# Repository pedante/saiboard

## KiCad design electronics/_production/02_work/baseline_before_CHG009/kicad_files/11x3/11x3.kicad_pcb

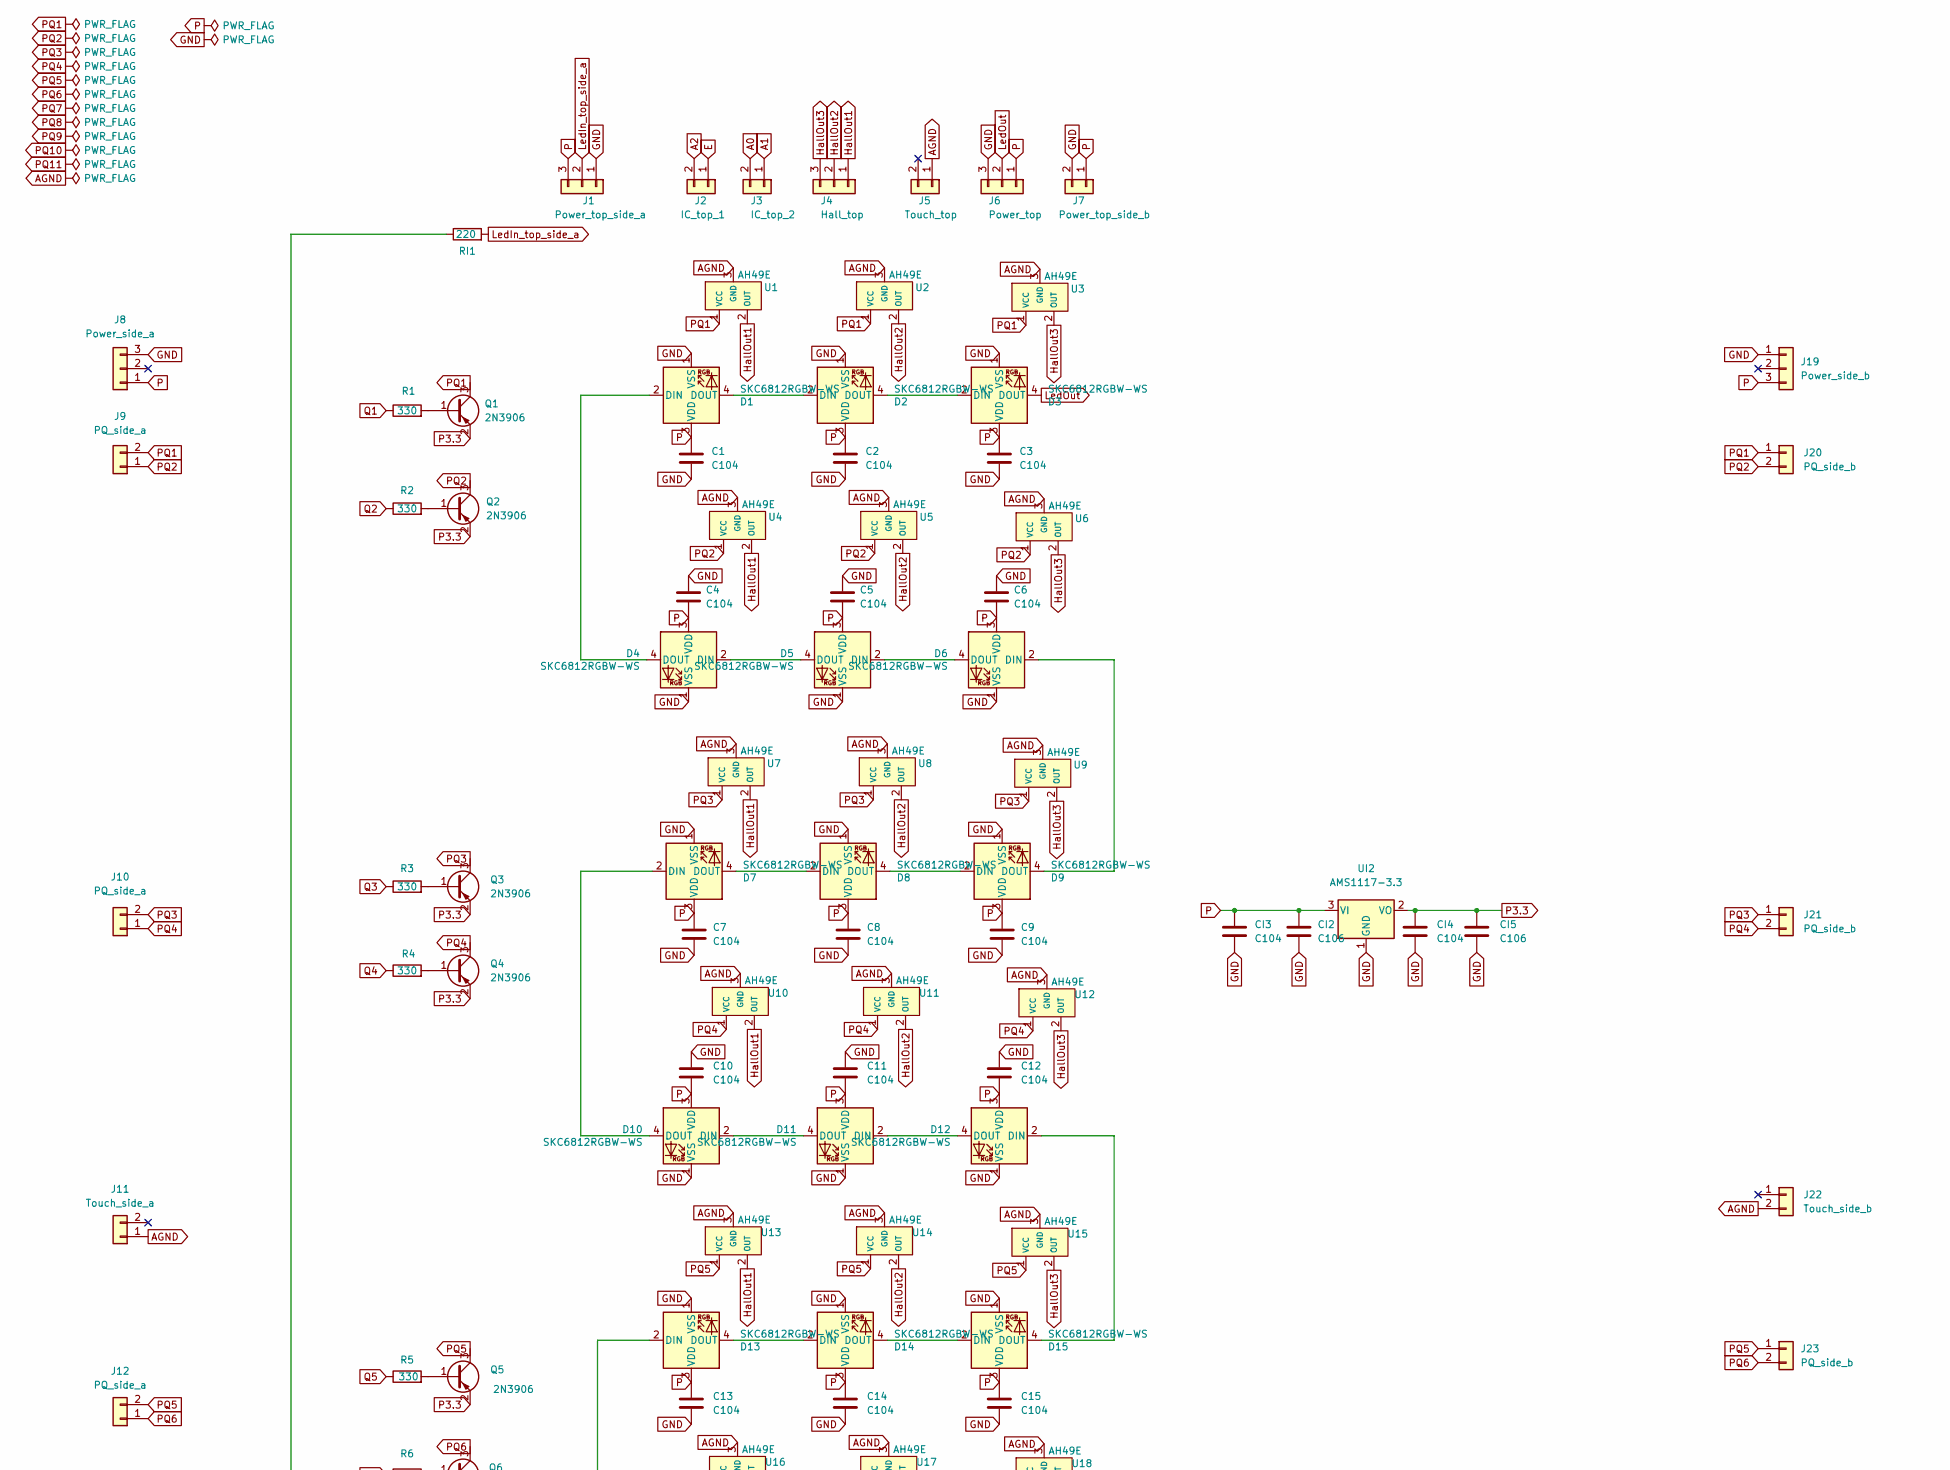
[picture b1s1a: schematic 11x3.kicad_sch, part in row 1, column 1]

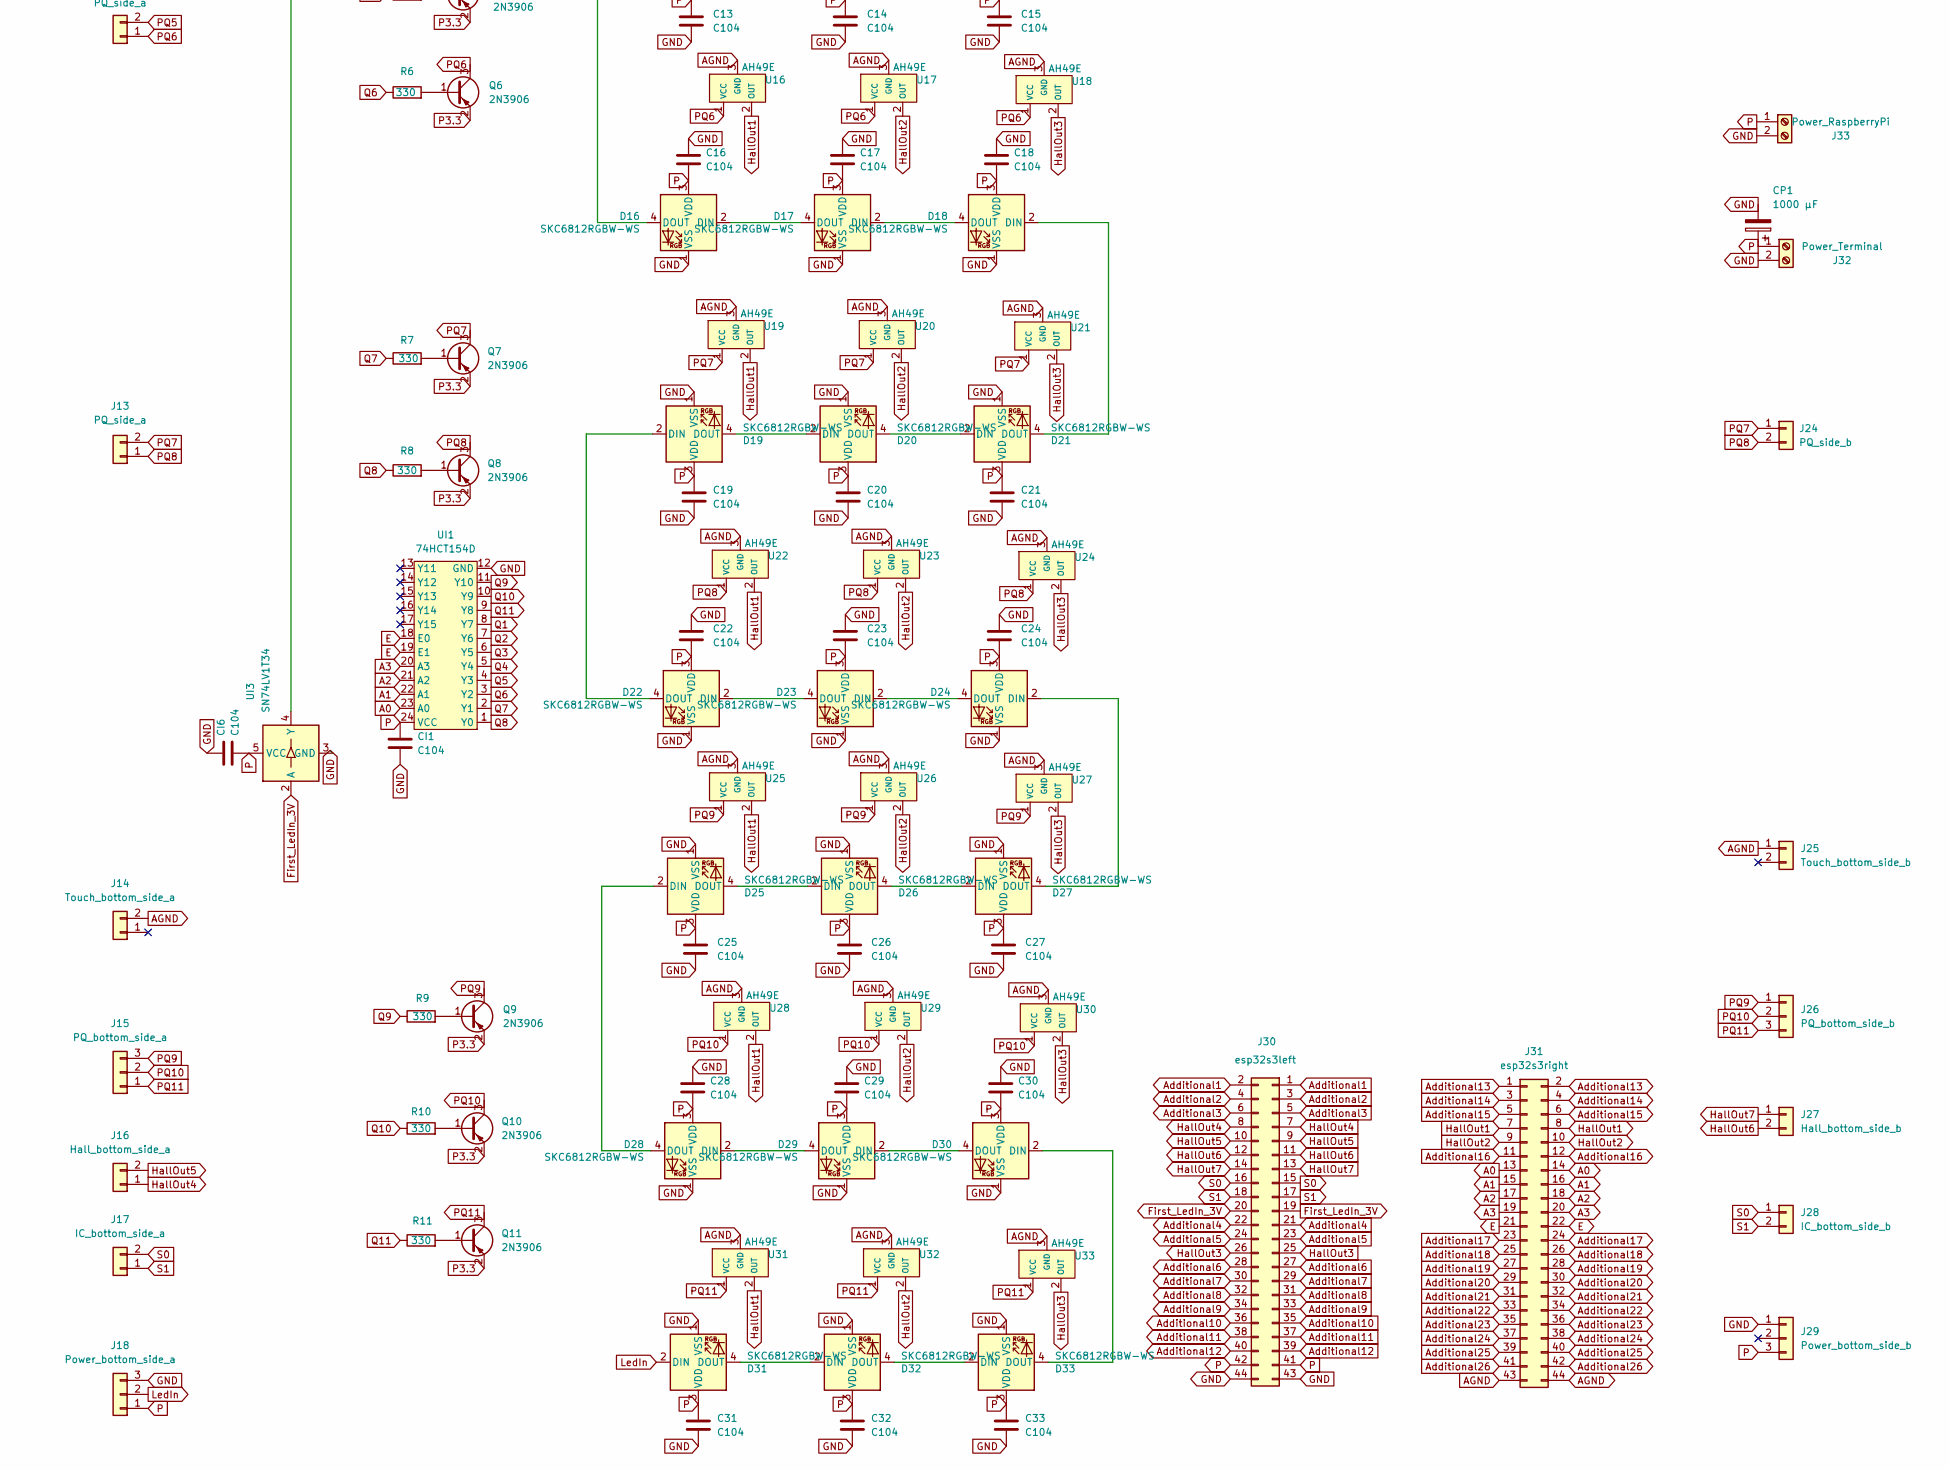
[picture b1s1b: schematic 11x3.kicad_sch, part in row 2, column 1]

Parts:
C1, C2, C3, C4, C5, C6, C7, C8, C9, C10, C11, C12, C13, C14, C15, C16, C17, C18, C19, C20, C21, C22, C23, C24, C25, C26, C27, C28, C29, C30, C31, C32, C33: C104; C_1206_3216Metric
CI1, CI3, CI4, CI6: C104; C_1206_3216Metric
CI2, CI5: C106; C_1206_3216Metric
CP1: 1000 µF; CP_Elec_10x10.5
D1, D2, D3, D4, D5, D6, D7, D8, D9, D10, D11, D12, D13, D14, D15, D16, D17, D18, D19, D20, D21, D22, D23, D24, D25, D26, D27, D28, D29, D30, D31, D32, D33: SKC6812RGBW-WS; LED_SK6812_PLCC4_5.0x5.0mm_P3.2mm; MPN SKC6812RGBW-WS; LCSC C5378724
J1: Power_top_side_a; PinSocket_1x03_P2.54mm_Horizontal_SMD
J2: IC_top_1; PinSocket_1x02_P2.54mm_Horizontal_SMD
J3: IC_top_2; PinSocket_1x02_P2.54mm_Horizontal_SMD
J4: Hall_top; PinSocket_1x03_P2.54mm_Horizontal_SMD
J5: Touch_top; PinSocket_1x02_P2.54mm_Horizontal_SMD
J6: Power_top; PinSocket_1x03_P2.54mm_Horizontal_SMD
J7: Power_top_side_b; PinSocket_1x02_P2.54mm_Horizontal_SMD
J8: Power_side_a; PinHeader_1x03_P2.54mm_Horizontal_SMD
J9, J10, J12, J13: PQ_side_a; PinHeader_1x02_P2.54mm_Horizontal_SMD
J11: Touch_side_a; PinHeader_1x02_P2.54mm_Horizontal_SMD
J14: Touch_bottom_side_a; PinHeader_1x02_P2.54mm_Horizontal_SMD
J15: PQ_bottom_side_a; PinHeader_1x03_P2.54mm_Horizontal_SMD
J16: Hall_bottom_side_a; PinHeader_1x02_P2.54mm_Horizontal_SMD
J17: IC_bottom_side_a; PinHeader_1x02_P2.54mm_Horizontal_SMD
J18: Power_bottom_side_a; PinHeader_1x03_P2.54mm_Horizontal_SMD
J19: Power_side_b; PinHeader_1x03_P2.54mm_Horizontal_SMD
J20, J21, J23, J24: PQ_side_b; PinHeader_1x02_P2.54mm_Horizontal_SMD
J22: Touch_side_b; PinHeader_1x02_P2.54mm_Horizontal_SMD
J25: Touch_bottom_side_b; PinHeader_1x02_P2.54mm_Horizontal_SMD
J26: PQ_bottom_side_b; PinHeader_1x03_P2.54mm_Horizontal_SMD
J27: Hall_bottom_side_b; PinHeader_1x02_P2.54mm_Horizontal_SMD
J28: IC_bottom_side_b; PinHeader_1x02_P2.54mm_Horizontal_SMD
J29: Power_bottom_side_b; PinHeader_1x03_P2.54mm_Horizontal_SMD
J30: esp32s3left; PinSocket_2x22_P2.54mm_Vertical_SMD
J31: esp32s3right; PinSocket_2x22_P2.54mm_Vertical_SMD
J32: Power_Terminal; Wago_2601-602
J33: Power_RaspberryPi; Wago_2601-602
Q1, Q2, Q3, Q4, Q5, Q6, Q7, Q8, Q9, Q10, Q11: 2N3906; SOT-23
R1, R2, R3, R4, R5, R6, R7, R8, R9, R10, R11: 330; R_1206_3216Metric
RI1: 220; R_1206_3216Metric
U1, U2, U3, U4, U5, U6, U7, U8, U9, U10, U11, U12, U13, U14, U15, U16, U17, U18, U19, U20, U21, U22, U23, U24, U25, U26, U27, U28, U29, U30, U31, U32, U33: AH49E; SOT-23
UI1: 74HCT154D; SOP-24_7.5x15.4mm_P1.27mm
UI2: AMS1117-3.3; SOT-223
UI3: SN74LV1T34; SOT-23-5

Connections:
A0: J3.2, J31.13, J31.14, UI1.23 (A0)
A1: J3.1, J31.15, J31.16, UI1.22 (A1)
A2: J2.2, J31.17, J31.18, UI1.21 (A2)
A3: J31.19, J31.20, UI1.20 (A3)
AGND: J5.1, J11.1, J14.2, J22.2, J25.1, J31.43, J31.44, U1.3 (GND), U2.3 (GND), U3.3 (GND), U4.3 (GND), U5.3 (GND), U6.3 (GND), U7.3 (GND), U8.3 (GND), U9.3 (GND), U10.3 (GND), U11.3 (GND), U12.3 (GND), U13.3 (GND), U14.3 (GND), U15.3 (GND), U16.3 (GND), U17.3 (GND), U18.3 (GND), U19.3 (GND), U20.3 (GND), U21.3 (GND), U22.3 (GND), U23.3 (GND), U24.3 (GND), U25.3 (GND), U26.3 (GND), U27.3 (GND), U28.3 (GND), U29.3 (GND), U30.3 (GND), U31.3 (GND), U32.3 (GND), U33.3 (GND)
Additional1: J30.1, J30.2
Additional2: J30.3, J30.4
Additional3: J30.5, J30.6
Additional4: J30.21, J30.22
Additional5: J30.23, J30.24
Additional6: J30.27, J30.28
Additional7: J30.29, J30.30
Additional8: J30.31, J30.32
Additional9: J30.33, J30.34
Additional10: J30.35, J30.36
Additional11: J30.37, J30.38
Additional12: J30.39, J30.40
Additional13: J31.1, J31.2
Additional14: J31.3, J31.4
Additional15: J31.5, J31.6
Additional16: J31.11, J31.12
Additional17: J31.23, J31.24
Additional18: J31.25, J31.26
Additional19: J31.27, J31.28
Additional20: J31.29, J31.30
Additional21: J31.31, J31.32
Additional22: J31.33, J31.34
Additional23: J31.35, J31.36
Additional24: J31.37, J31.38
Additional25: J31.39, J31.40
Additional26: J31.41, J31.42
E: J2.1, J31.21, J31.22, UI1.18 (E0), UI1.19 (E1)
First_LedIn_3V: J30.19, J30.20, UI3.2 (A)
GND: C1.2, C2.2, C3.2, C4.2, C5.2, C6.2, C7.2, C8.2, C9.2, C10.2, C11.2, C12.2, C13.2, C14.2, C15.2, C16.2, C17.2, C18.2, C19.2, C20.2, C21.2, C22.2, C23.2, C24.2, C25.2, C26.2, C27.2, C28.2, C29.2, C30.2, C31.2, C32.2, C33.2, CI1.1, CI2.1, CI3.1, CI4.1, CI5.1, CI6.2, CP1.2, D1.1 (VSS), D2.1 (VSS), D3.1 (VSS), D4.1 (VSS), D5.1 (VSS), D6.1 (VSS), D7.1 (VSS), D8.1 (VSS), D9.1 (VSS), D10.1 (VSS), D11.1 (VSS), D12.1 (VSS), D13.1 (VSS), D14.1 (VSS), D15.1 (VSS), D16.1 (VSS), D17.1 (VSS), D18.1 (VSS), D19.1 (VSS), D20.1 (VSS), D21.1 (VSS), D22.1 (VSS), D23.1 (VSS), D24.1 (VSS), D25.1 (VSS), D26.1 (VSS), D27.1 (VSS), D28.1 (VSS), D29.1 (VSS), D30.1 (VSS), D31.1 (VSS), D32.1 (VSS), D33.1 (VSS), J1.1, J6.3, J7.2, J8.3, J18.3, J19.1, J29.1, J30.43, J30.44, J32.2, J33.2, UI1.12 (GND), UI2.1 (GND), UI3.3 (GND)
HallOut1: J4.1, J31.7, J31.8, U1.2 (OUT), U4.2 (OUT), U7.2 (OUT), U10.2 (OUT), U13.2 (OUT), U16.2 (OUT), U19.2 (OUT), U22.2 (OUT), U25.2 (OUT), U28.2 (OUT), U31.2 (OUT)
HallOut2: J4.2, J31.9, J31.10, U2.2 (OUT), U5.2 (OUT), U8.2 (OUT), U11.2 (OUT), U14.2 (OUT), U17.2 (OUT), U20.2 (OUT), U23.2 (OUT), U26.2 (OUT), U29.2 (OUT), U32.2 (OUT)
HallOut3: J4.3, J30.25, J30.26, U3.2 (OUT), U6.2 (OUT), U9.2 (OUT), U12.2 (OUT), U15.2 (OUT), U18.2 (OUT), U21.2 (OUT), U24.2 (OUT), U27.2 (OUT), U30.2 (OUT), U33.2 (OUT)
HallOut4: J16.1, J30.7, J30.8
HallOut5: J16.2, J30.9, J30.10
HallOut6: J27.2, J30.11, J30.12
HallOut7: J27.1, J30.13, J30.14
LedIn: D31.2 (DIN), J18.2
LedIn_top_side_a: J1.2, RI1.2
LedOut: D3.4 (DOUT), J6.2
unnamed: D1.2 (DIN), D4.4 (DOUT)
unnamed: D1.4 (DOUT), D2.2 (DIN)
unnamed: D2.4 (DOUT), D3.2 (DIN)
unnamed: D4.2 (DIN), D5.4 (DOUT)
unnamed: D5.2 (DIN), D6.4 (DOUT)
unnamed: D6.2 (DIN), D9.4 (DOUT)
unnamed: D7.4 (DOUT), D8.2 (DIN)
unnamed: D8.4 (DOUT), D9.2 (DIN)
unnamed: D10.2 (DIN), D11.4 (DOUT)
unnamed: D7.2 (DIN), D10.4 (DOUT)
unnamed: D11.2 (DIN), D12.4 (DOUT)
unnamed: D12.2 (DIN), D15.4 (DOUT)
unnamed: D13.2 (DIN), D16.4 (DOUT)
unnamed: D13.4 (DOUT), D14.2 (DIN)
unnamed: D14.4 (DOUT), D15.2 (DIN)
unnamed: D16.2 (DIN), D17.4 (DOUT)
unnamed: D17.2 (DIN), D18.4 (DOUT)
unnamed: D18.2 (DIN), D21.4 (DOUT)
unnamed: D19.2 (DIN), D22.4 (DOUT)
unnamed: D19.4 (DOUT), D20.2 (DIN)
unnamed: D20.4 (DOUT), D21.2 (DIN)
unnamed: D22.2 (DIN), D23.4 (DOUT)
unnamed: D23.2 (DIN), D24.4 (DOUT)
unnamed: D24.2 (DIN), D27.4 (DOUT)
unnamed: D25.2 (DIN), D28.4 (DOUT)
unnamed: D25.4 (DOUT), D26.2 (DIN)
unnamed: D26.4 (DOUT), D27.2 (DIN)
unnamed: D28.2 (DIN), D29.4 (DOUT)
unnamed: D29.2 (DIN), D30.4 (DOUT)
unnamed: D30.2 (DIN), D33.4 (DOUT)
unnamed: D31.4 (DOUT), D32.2 (DIN)
unnamed: D32.4 (DOUT), D33.2 (DIN)
unnamed: Q1.1 (B), R1.2
unnamed: Q2.1 (B), R2.2
unnamed: Q3.1 (B), R3.2
unnamed: Q4.1 (B), R4.2
unnamed: Q5.1 (B), R5.2
unnamed: Q6.1 (B), R6.2
unnamed: Q7.1 (B), R7.2
unnamed: Q8.1 (B), R8.2
unnamed: Q9.1 (B), R9.2
unnamed: Q10.1 (B), R10.2
unnamed: Q11.1 (B), R11.2
unnamed: RI1.1, UI3.4 (Y)
P: C1.1, C2.1, C3.1, C4.1, C5.1, C6.1, C7.1, C8.1, C9.1, C10.1, C11.1, C12.1, C13.1, C14.1, C15.1, C16.1, C17.1, C18.1, C19.1, C20.1, C21.1, C22.1, C23.1, C24.1, C25.1, C26.1, C27.1, C28.1, C29.1, C30.1, C31.1, C32.1, C33.1, CI1.2, CI2.2, CI3.2, CI6.1, CP1.1, D1.3 (VDD), D2.3 (VDD), D3.3 (VDD), D4.3 (VDD), D5.3 (VDD), D6.3 (VDD), D7.3 (VDD), D8.3 (VDD), D9.3 (VDD), D10.3 (VDD), D11.3 (VDD), D12.3 (VDD), D13.3 (VDD), D14.3 (VDD), D15.3 (VDD), D16.3 (VDD), D17.3 (VDD), D18.3 (VDD), D19.3 (VDD), D20.3 (VDD), D21.3 (VDD), D22.3 (VDD), D23.3 (VDD), D24.3 (VDD), D25.3 (VDD), D26.3 (VDD), D27.3 (VDD), D28.3 (VDD), D29.3 (VDD), D30.3 (VDD), D31.3 (VDD), D32.3 (VDD), D33.3 (VDD), J1.3, J6.1, J7.1, J8.1, J18.1, J19.3, J29.3, J30.41, J30.42, J32.1, J33.1, UI1.24 (VCC), UI2.3 (VI), UI3.5 (VCC)
P3.3: CI4.2, CI5.2, Q1.2 (E), Q2.2 (E), Q3.2 (E), Q4.2 (E), Q5.2 (E), Q6.2 (E), Q7.2 (E), Q8.2 (E), Q9.2 (E), Q10.2 (E), Q11.2 (E), UI2.2 (VO)
PQ1: J9.2, J20.1, Q1.3 (C), U1.1 (VCC), U2.1 (VCC), U3.1 (VCC)
PQ2: J9.1, J20.2, Q2.3 (C), U4.1 (VCC), U5.1 (VCC), U6.1 (VCC)
PQ3: J10.2, J21.1, Q3.3 (C), U7.1 (VCC), U8.1 (VCC), U9.1 (VCC)
PQ4: J10.1, J21.2, Q4.3 (C), U10.1 (VCC), U11.1 (VCC), U12.1 (VCC)
PQ5: J12.2, J23.1, Q5.3 (C), U13.1 (VCC), U14.1 (VCC), U15.1 (VCC)
PQ6: J12.1, J23.2, Q6.3 (C), U16.1 (VCC), U17.1 (VCC), U18.1 (VCC)
PQ7: J13.2, J24.1, Q7.3 (C), U19.1 (VCC), U20.1 (VCC), U21.1 (VCC)
PQ8: J13.1, J24.2, Q8.3 (C), U22.1 (VCC), U23.1 (VCC), U24.1 (VCC)
PQ9: J15.3, J26.1, Q9.3 (C), U25.1 (VCC), U26.1 (VCC), U27.1 (VCC)
PQ10: J15.2, J26.2, Q10.3 (C), U28.1 (VCC), U29.1 (VCC), U30.1 (VCC)
PQ11: J15.1, J26.3, Q11.3 (C), U31.1 (VCC), U32.1 (VCC), U33.1 (VCC)
Q1: R1.1, UI1.8 (Y7)
Q2: R2.1, UI1.7 (Y6)
Q3: R3.1, UI1.6 (Y5)
Q4: R4.1, UI1.5 (Y4)
Q5: R5.1, UI1.4 (Y3)
Q6: R6.1, UI1.3 (Y2)
Q7: R7.1, UI1.2 (Y1)
Q8: R8.1, UI1.1 (Y0)
Q9: R9.1, UI1.11 (Y10)
Q10: R10.1, UI1.10 (Y9)
Q11: R11.1, UI1.9 (Y8)
S0: J17.2, J28.1, J30.15, J30.16
S1: J17.1, J28.2, J30.17, J30.18

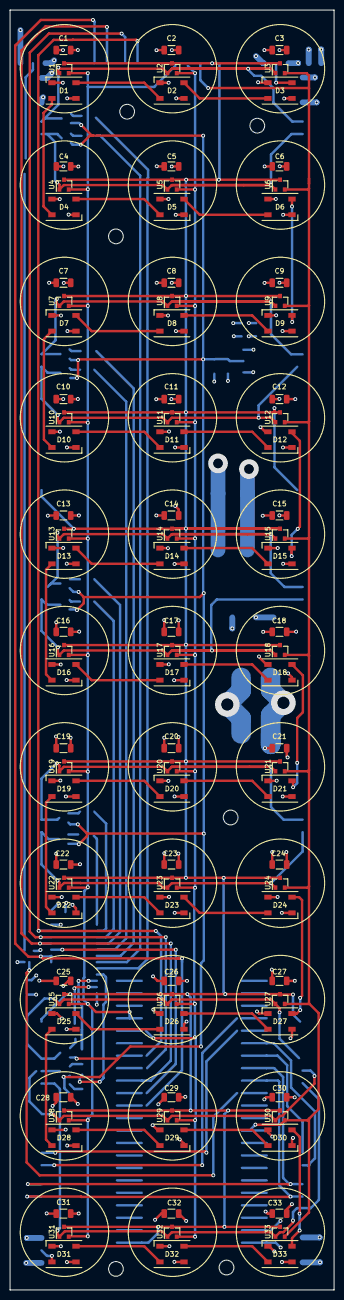
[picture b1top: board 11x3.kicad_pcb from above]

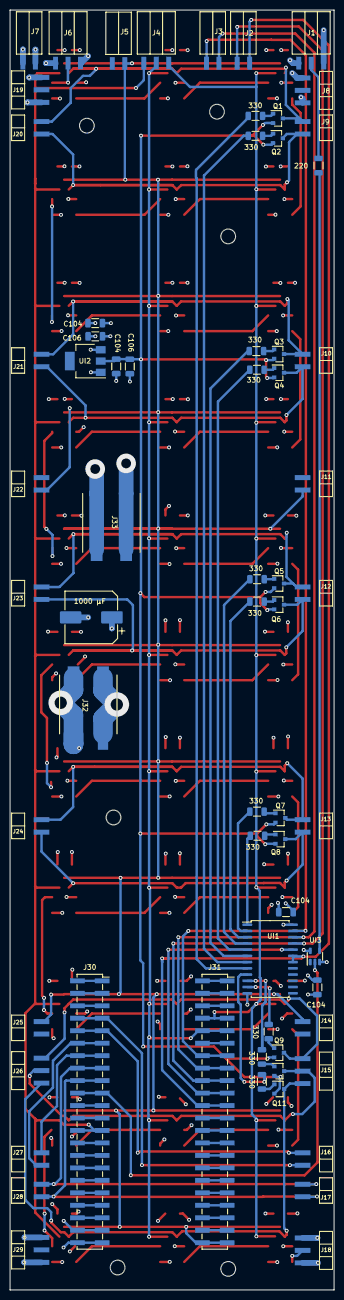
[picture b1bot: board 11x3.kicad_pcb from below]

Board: 4 copper layers, 66.0 x 260.7 mm, 171 parts (66 on the bottom side), 114 nets.

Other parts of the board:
M1, M2, M5, M6, M6#2, M6#3: MountingHole_3mm

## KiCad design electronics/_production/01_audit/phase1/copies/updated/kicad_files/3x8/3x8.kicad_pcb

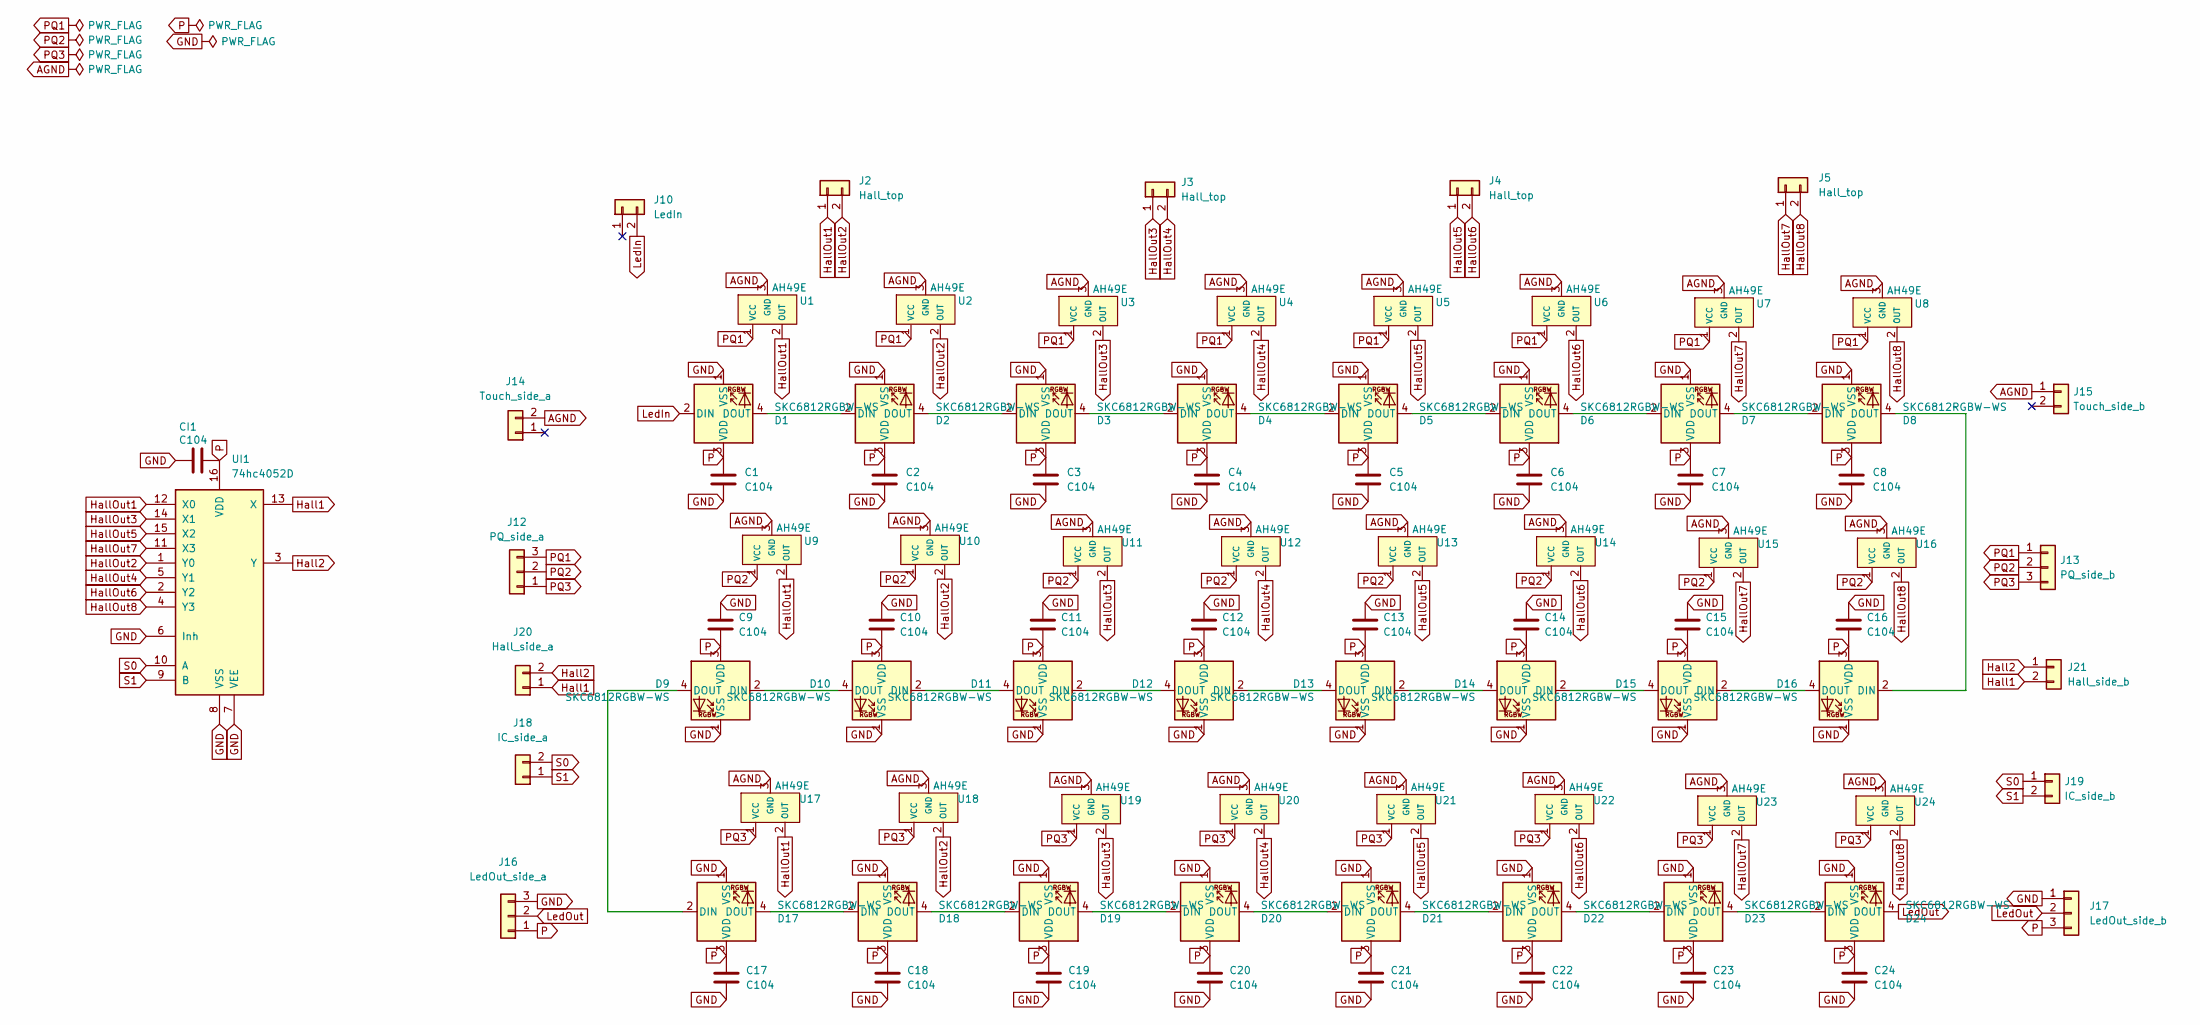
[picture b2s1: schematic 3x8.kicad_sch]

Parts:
C1, C2, C3, C4, C5, C6, C7, C8, C9, C10, C11, C12, C13, C14, C15, C16, C17, C18, C19, C20, C21, C22, C23, C24: C104; C_1206_3216Metric
CI1: C104; C_1206_3216Metric
D1, D2, D3, D4, D5, D6, D7, D8, D9, D10, D11, D12, D13, D14, D15, D16, D17, D18, D19, D20, D21, D22, D23, D24: SKC6812RGBW-WS; LED_SK6812_PLCC4_5.0x5.0mm_P3.2mm; MPN SKC6812RGBW-WS; LCSC C5378724
J2, J3, J4, J5: Hall_top; PinHeader_1x02_P2.54mm_Horizontal_SMD
J10: LedIn; PinHeader_1x02_P2.54mm_Horizontal_SMD
J12: PQ_side_a; PinSocket_1x03_P2.54mm_Horizontal_SMD
J13: PQ_side_b; PinSocket_1x03_P2.54mm_Horizontal_SMD
J14: Touch_side_a; PinSocket_1x02_P2.54mm_Horizontal_SMD
J15: Touch_side_b; PinSocket_1x02_P2.54mm_Horizontal_SMD
J16: LedOut_side_a; PinSocket_1x03_P2.54mm_Horizontal_SMD
J17: LedOut_side_b; PinSocket_1x03_P2.54mm_Horizontal_SMD
J18: IC_side_a; PinSocket_1x02_P2.54mm_Horizontal_SMD
J19: IC_side_b; PinSocket_1x02_P2.54mm_Horizontal_SMD
J20: Hall_side_a; PinSocket_1x02_P2.54mm_Horizontal_SMD
J21: Hall_side_b; PinSocket_1x02_P2.54mm_Horizontal_SMD
U1, U2, U3, U4, U5, U6, U7, U8, U9, U10, U11, U12, U13, U14, U15, U16, U17, U18, U19, U20, U21, U22, U23, U24: AH49E; SOT-23
UI1: 74hc4052D; SO-16_3.9x9.9mm_P1.27mm

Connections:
AGND: J14.2, J15.1, U1.3 (GND), U2.3 (GND), U3.3 (GND), U4.3 (GND), U5.3 (GND), U6.3 (GND), U7.3 (GND), U8.3 (GND), U9.3 (GND), U10.3 (GND), U11.3 (GND), U12.3 (GND), U13.3 (GND), U14.3 (GND), U15.3 (GND), U16.3 (GND), U17.3 (GND), U18.3 (GND), U19.3 (GND), U20.3 (GND), U21.3 (GND), U22.3 (GND), U23.3 (GND), U24.3 (GND)
GND: C1.2, C2.2, C3.2, C4.2, C5.2, C6.2, C7.2, C8.2, C9.2, C10.2, C11.2, C12.2, C13.2, C14.2, C15.2, C16.2, C17.2, C18.2, C19.2, C20.2, C21.2, C22.2, C23.2, C24.2, CI1.2, D1.1 (VSS), D2.1 (VSS), D3.1 (VSS), D4.1 (VSS), D5.1 (VSS), D6.1 (VSS), D7.1 (VSS), D8.1 (VSS), D9.1 (VSS), D10.1 (VSS), D11.1 (VSS), D12.1 (VSS), D13.1 (VSS), D14.1 (VSS), D15.1 (VSS), D16.1 (VSS), D17.1 (VSS), D18.1 (VSS), D19.1 (VSS), D20.1 (VSS), D21.1 (VSS), D22.1 (VSS), D23.1 (VSS), D24.1 (VSS), J16.3, J17.1, UI1.6 (Inh), UI1.7 (VEE), UI1.8 (VSS)
Hall1: J20.1, J21.2, UI1.13 (X)
Hall2: J20.2, J21.1, UI1.3 (Y)
HallOut1: J2.1, U1.2 (OUT), U9.2 (OUT), U17.2 (OUT), UI1.12 (X0)
HallOut2: J2.2, U2.2 (OUT), U10.2 (OUT), U18.2 (OUT), UI1.1 (Y0)
HallOut3: J3.1, U3.2 (OUT), U11.2 (OUT), U19.2 (OUT), UI1.14 (X1)
HallOut4: J3.2, U4.2 (OUT), U12.2 (OUT), U20.2 (OUT), UI1.5 (Y1)
HallOut5: J4.1, U5.2 (OUT), U13.2 (OUT), U21.2 (OUT), UI1.15 (X2)
HallOut6: J4.2, U6.2 (OUT), U14.2 (OUT), U22.2 (OUT), UI1.2 (Y2)
HallOut7: J5.1, U7.2 (OUT), U15.2 (OUT), U23.2 (OUT), UI1.11 (X3)
HallOut8: J5.2, U8.2 (OUT), U16.2 (OUT), U24.2 (OUT), UI1.4 (Y3)
LedIn: D1.2 (DIN), J10.2
LedOut: D24.4 (DOUT), J16.2, J17.2
unnamed: D1.4 (DOUT), D2.2 (DIN)
unnamed: D2.4 (DOUT), D3.2 (DIN)
unnamed: D3.4 (DOUT), D4.2 (DIN)
unnamed: D4.4 (DOUT), D5.2 (DIN)
unnamed: D5.4 (DOUT), D6.2 (DIN)
unnamed: D6.4 (DOUT), D7.2 (DIN)
unnamed: D7.4 (DOUT), D8.2 (DIN)
unnamed: D10.2 (DIN), D11.4 (DOUT)
unnamed: D9.2 (DIN), D10.4 (DOUT)
unnamed: D11.2 (DIN), D12.4 (DOUT)
unnamed: D12.2 (DIN), D13.4 (DOUT)
unnamed: D13.2 (DIN), D14.4 (DOUT)
unnamed: D14.2 (DIN), D15.4 (DOUT)
unnamed: D15.2 (DIN), D16.4 (DOUT)
unnamed: D8.4 (DOUT), D16.2 (DIN)
unnamed: D9.4 (DOUT), D17.2 (DIN)
unnamed: D17.4 (DOUT), D18.2 (DIN)
unnamed: D18.4 (DOUT), D19.2 (DIN)
unnamed: D19.4 (DOUT), D20.2 (DIN)
unnamed: D20.4 (DOUT), D21.2 (DIN)
unnamed: D21.4 (DOUT), D22.2 (DIN)
unnamed: D22.4 (DOUT), D23.2 (DIN)
unnamed: D23.4 (DOUT), D24.2 (DIN)
P: C1.1, C2.1, C3.1, C4.1, C5.1, C6.1, C7.1, C8.1, C9.1, C10.1, C11.1, C12.1, C13.1, C14.1, C15.1, C16.1, C17.1, C18.1, C19.1, C20.1, C21.1, C22.1, C23.1, C24.1, CI1.1, D1.3 (VDD), D2.3 (VDD), D3.3 (VDD), D4.3 (VDD), D5.3 (VDD), D6.3 (VDD), D7.3 (VDD), D8.3 (VDD), D9.3 (VDD), D10.3 (VDD), D11.3 (VDD), D12.3 (VDD), D13.3 (VDD), D14.3 (VDD), D15.3 (VDD), D16.3 (VDD), D17.3 (VDD), D18.3 (VDD), D19.3 (VDD), D20.3 (VDD), D21.3 (VDD), D22.3 (VDD), D23.3 (VDD), D24.3 (VDD), J16.1, J17.3, UI1.16 (VDD)
PQ1: J12.3, J13.1, U1.1 (VCC), U2.1 (VCC), U3.1 (VCC), U4.1 (VCC), U5.1 (VCC), U6.1 (VCC), U7.1 (VCC), U8.1 (VCC)
PQ2: J12.2, J13.2, U9.1 (VCC), U10.1 (VCC), U11.1 (VCC), U12.1 (VCC), U13.1 (VCC), U14.1 (VCC), U15.1 (VCC), U16.1 (VCC)
PQ3: J12.1, J13.3, U17.1 (VCC), U18.1 (VCC), U19.1 (VCC), U20.1 (VCC), U21.1 (VCC), U22.1 (VCC), U23.1 (VCC), U24.1 (VCC)
S0: J18.2, J19.1, UI1.10 (A)
S1: J18.1, J19.2, UI1.9 (B)

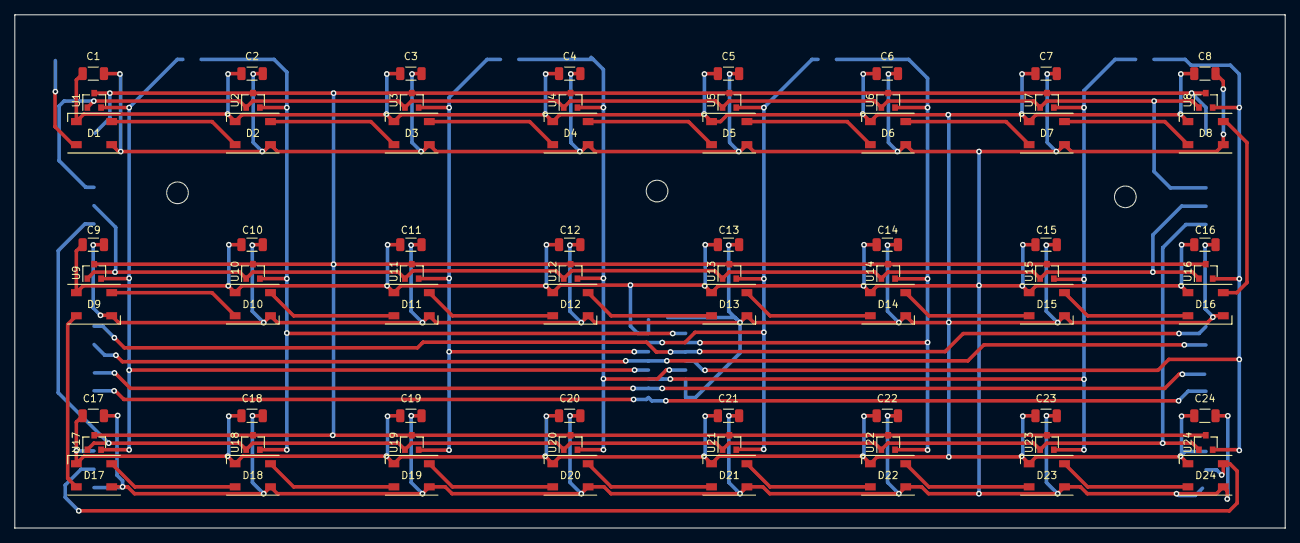
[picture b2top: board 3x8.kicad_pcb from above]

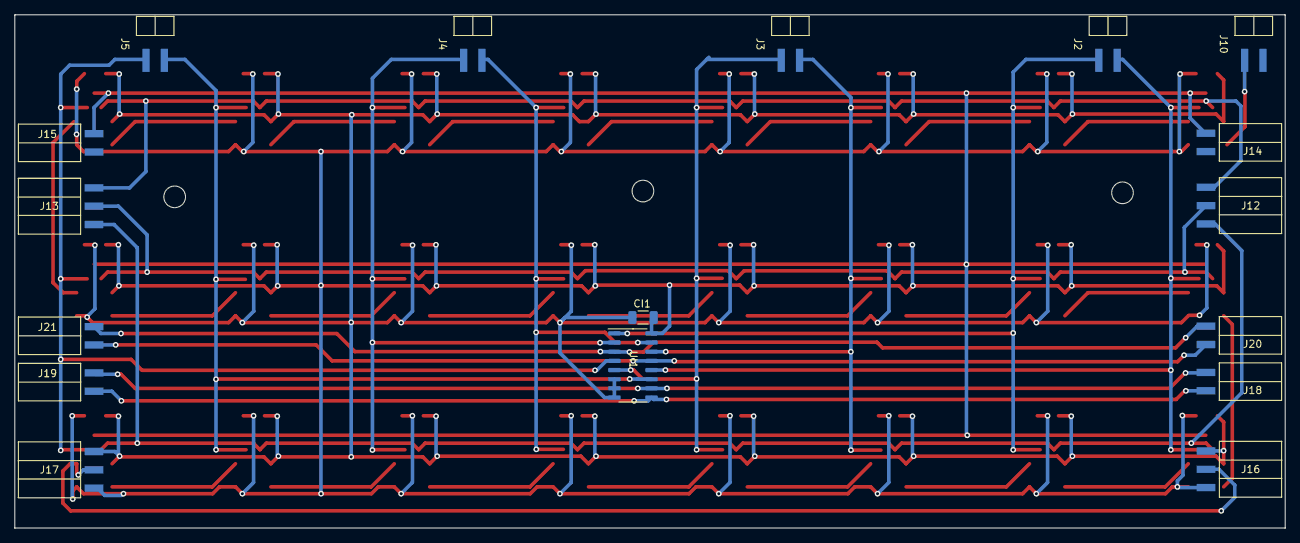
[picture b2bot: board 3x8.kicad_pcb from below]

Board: 2 copper layers, 176.0 x 71.1 mm, 92 parts (17 on the bottom side), 43 nets.

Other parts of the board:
M1, M2, M3: MountingHole_3mm
